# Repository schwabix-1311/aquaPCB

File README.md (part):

# aquaPCB

Raspberry Pi base board for [aquaPi](https://github.com/schwabix-1311/aquaPI), the
modular aquarium controller. v2 is a head unit that also fits Robo-Tank v3 modules, cables
and power bars (through adapter cables): one board with a 12-24 V supply input, six 5 A
power outputs, DC and LED ports with 7 PWM channels each, two power bar ports, six sensor
inputs, 1-Wire, four 0-5 V analog sockets on an ADS1115, and headers for a small display
and I²C add-ons. A cheaper **light** assembly of the same PCB is for aquaPi only - it is
**not** a Robo-Tank replacement (see [Light variant](#light-variant-aquapi-only)).

Most channels are plain GPIO, hardware PWM, 1-Wire or I²C ports that aquaPi discovers by
itself and offers in its Wiring editor. The channels on the two PCA9685 PWM expanders
(DC/LED ports, Q2/Q3/Q5/Q6, power bars) use aquaPi's PCA9685 driver, which finds the chips by
an I²C scan (0x40-0x47) and offers only the ports of the chips it finds. It ships with aquaPi 1.0
(branch `release/1.0`) and still has to be tested on real hardware.

> Status: **v2 layout complete** on `main` (2026-10-23): schematic ERC clean, board fully
> routed, DRC without errors (silkscreen warnings only; the deliberate overlap of the ADC
> socket courtyards is waived by a rule in `kicad/aquaPCB.kicad_dru`). No prototypes built
> yet; the [first prototype order](#first-prototype-order-5-light-boards-2-upgrade-kits) (5 light
> boards, 2 upgrade kits) is planned, the [open questions](#open-questions-asked-to-robo-tank-or-measure)
> to Robo-Tank are still open. v1 (tag `v1.0.1`, branch `release/v1`, layout complete,
> DRC clean) stays the restart point. Sections marked *v1* below still describe v1; v2
> changes are in the [v2 plan](#v2-plan-robo-tank-v3-compatible-head-unit).
> Not a beginner kit: SMD parts are assembled by the PCB fab (JLCPCB economic PCBA);
> only through-hole connectors are hand-soldered.

## Key figures

```
Supply          12-24 V DC, 8 A max total, 10 A fuse (parts rated >= 40 V; 24 V not yet validated)
Pi              Zero 2 W plugged on face-up, powered from the board; Pi 3 via 40-pin ribbon;
                Pi 4/5 with their own power supply (JP1 open)
Power outputs   6x low-side MOSFET, 5 A each, 6.5 A total (up to ~7 A, see current budget);
                Q1/Q4 on hardware PWM, Q2/Q3/Q5/Q6 on PCA9685 #1 (shared with LED port pins 2..5)
PWM ports       DC port + LED port, 7 channels each, 0-5 V PWM (PCA9685 #1, 74HCT244),
                2x4 box headers with the Robo-Tank v3 pinout
Power bars      2 ports x 8 outlets, 3.3 V logic (PCA9685 #2), 2x5 box headers for an IDC DB9
                adapter; 2 hardware backup float inputs for bar 1 outlets 1/2
Inputs          6x sensor inputs, 5 V tolerant (GPIO 5,6,20-23), 2x4 box header
1-Wire          GPIO4, 1x3 pin header (bus: several sensors on one header)
Analog          ADS1115, 16 bit, 4x 0-5 V sockets; pH/ORP amplifiers on add-on modules
Expansion       2x 3.3 V I2C header, SPI display header
Board           100 x 100 mm, 2 layers, 1 oz Cu
```

No mains voltage on this board. Mains loads (heater, pumps) are switched by external
SSRs or relay modules on the Q outputs, or by Robo-Tank power bars.

## Block diagram

*v1 - for v2 see [aquaPCB v2 connectors](#aquapcb-v2-connectors) and [v1 -> v2 changes](#v1---v2-changes).*

```
 12 V in ──[fuse 8A]───[rev.pol. P-FET]──┬──[TVS]── V_IN rail ─────────────┐
                                         │                                  │
                                    [buck 5V/3A]──┬── jumper "5V→Pi" ──> Pi 5V
                                                  │                         │
                                             [LDO 3V3]── ADC, sensors, display
                                                                            │
   Pi GPIO ──> [74HCT244, 5V] ──> gate ──> Q1..Q6 MOSFET ──> terminals (+V_IN / OUT)
   Pi GPIO ──> [ULN2803A] ─────────────> S1..S4 ──> terminals (+5V|+V_IN / OUT)
   IN1..IN4 terminals ──[1k + clamp, 10k pull-up]──> Pi GPIO
   1-Wire terminals ──[4k7 pull-up, ESD]──> GPIO4
   I2C (GPIO2/3) ──> 2x I2C header
                └──> ADS1115 ──< pH buffer ──< BNC ;  module input (0..5 V) ;  AIN3 terminal
   SPI0 + DC/RST ──> display header
```

## Pin map (BCM numbering)

*v1 - for v2 see [aquaPCB v2 connectors](#aquapcb-v2-connectors) and [v1 -> v2 changes](#v1---v2-changes).*

Outputs sit on GPIO 9 and above only: those pins default to pull-down at boot, so no load
switches on while the Pi boots. GPIO 0..8 default to pull-up and are used for inputs and
buses only.

```
GPIO  function            GPIO  function
 0    reserved (ID EEPROM) 14    unused (not connected)
 1    reserved (ID EEPROM) 15    unused (not connected)
 2    I2C SDA              16    Q5  power out
 3    I2C SCL              17    S1  SSR out
 4    1-Wire               18    Q1  power out, PWM0 (light)
 5    IN1                  19    Q4  power out, PWM1 (fan)
 6    IN2                  20    IN3
 7    SPI CE1              21    IN4
 8    SPI CE0              22    S2  SSR out
 9    SPI MISO             23    S3  SSR out
10    SPI MOSI             24    display RST
11    SPI SCLK             25    display DC
12    Q2  power out        26    Q6  power out
13    Q3  power out        27    S4  SSR out
```

All GPIOs except 14/15 are in use (14/15 stay free: no UART console, customers rarely
have a USB-serial adapter). Further expansion goes over I²C (e.g. PCA9685 PWM breakout,
MCP23017 IO expander).

Raspberry Pi OS settings: `dtoverlay=pwm-2chan,pin=18,func=2,pin2=19,func2=2`,
`dtoverlay=w1-gpio,gpiopin=4`, `dtparam=i2c_arm=on`, `dtparam=spi=on` (display only).

## Circuit blocks

*v1 - for v2 see [aquaPCB v2 connectors](#aquapcb-v2-connectors) and [v1 -> v2 changes](#v1---v2-changes).*

### Power input
- 2-pin push-in terminal, 8 A fuse in a Littelfuse OMNI-BLOK holder (replaceable Nano2
  fuse; common 5x20 mm PCB holders are only rated 6.3 A). 8 A is the board's total current
  limit, set by the terminals' rating (8 A IEC per contact).
- Reverse-polarity protection: P-channel MOSFET in the positive line, gate via resistor
  to GND with a 15 V zener clamp (needed only above ~18 V, kept for 24 V readiness).
- TVS SMBJ33A across V_IN, bulk electrolytic 470 µF / 50 V.

### 5 V and 3.3 V
- Buck converter TPS54360B (60 V input, 3.5 A), non-synchronous with SS54 catch diode and
  10 µH / 5.4 A inductor, set to 5 V / 3 A. 3 A covers Pi Zero 2 W through Pi 4.
  Based on TI's 5 V design example (datasheet SNVSB93, fig. 32), values moved to JLC basic
  parts: RT 150 k (644 kHz), feedback 12 k / 2.2 k (5.16 V), compensation 12 k + 10 nF,
  47 pF, 2x 47 µF output. EN left open (internal 4.3 V UVLO).
- Jumper "5V→Pi" feeds the Pi through its GPIO header 5 V pins. Leave it **open** when the
  Pi has its own USB power supply (always for Pi 5).
- 3.3 V LDO (AMS1117-3.3) from 5 V for ADC, 1-Wire, inputs and display, so peripherals
  don't load the Pi's own regulator.

### Power outputs Q1..Q6
Identical low-side switches, terminal pair +V_IN / OUT per channel, 5 A each (8 A in total
for the whole board).
- 74HCT244 on 5 V as gate driver: accepts 3.3 V logic (V_IH 2.0 V), drives gates at 5 V,
  and keeps the Pi's GPIOs isolated from the power stage.
- 100 Ω gate resistor, 10 kΩ gate pull-down (output stays off when the Pi is absent or
  booting), logic-level N-MOSFET, 40 V, DPAK (e.g. AOD4184A, ~9 mΩ at V_GS 4.5 V).
- SS54 Schottky freewheel diode OUT → +V_IN for fans, pumps, solenoids.
- Status LED per channel.
- Q1/Q4 on hardware PWM (GPIO18/19) for dimming LED lamps and 2-wire fans. 4-wire PC-fan
  PWM input is not supported. The GPIO order Q1 18, Q2 12, Q3 13, Q4 19 follows the Pi
  header, so the GPIO → 74HCT244 → gate lines route without crossings.

Why not drive the MOSFET directly from the GPIO (e.g. IRLB8721)? It works with typical
parts, but R_DS(on) is only specified from V_GS 4.5 V while V_th may reach 2.35 V, so a
worst-case part runs half-on at 3.3 V and heats up; the gate floats during boot; a
gate-drain short puts the load supply onto the Pi; and 30 V V_DS leaves no margin for 24 V.
The buffer costs about €0.60 per board.

### SSR outputs S1..S4
- ULN2803A (SOIC-18), open-collector sink with built-in flyback diodes.
- Terminal pair per channel: supply (+5 V or +V_IN, selected by jumper) and OUT.
- Drives SSRs with 3..32 V DC control input or relay modules.
- The four unused ULN2803A channels stay unconnected (inputs open; the internal resistors keep
  them off).

### Digital inputs IN1..IN4
3-pin terminal 3V3 / IN / GND for float switches, level sensors, push buttons.
1 kΩ series resistor, 10 kΩ pull-up to 3.3 V, BAT54S clamp to 3.3 V and GND.

### 1-Wire
GPIO4 with 4.7 kΩ pull-up to 3.3 V; one 3-pin terminal (GND / DQ / 3V3), so both
3-wire and parasitic-powered (GND / DQ only) DS18B20 sensors work. ESD protection diode.

### ADS1115 and pH
- ADS1115 on 3.3 V directly on the Pi's I²C bus (matching logic levels, no level shifter),
  address 0x48 by default, 0x49 by solder jumper.
- All inputs are read **single-ended**, as aquaPi's ADS1115 driver does today.
- Requirements behind this design: good probe lifetime; ~0.1 pH stability is enough, since
  aquaPi's ScaleAux calibration removes offset and slope. Derived from the hand-built
  controller (PH-4502C amplifier with 10 MΩ / 4.7 nF styroflex input filter, probe life > 2
  years).
- AIN0: on-board pH amplifier, like the PH-4502C but with a low-leakage input. Right-angle BNC
  jack at the left board edge (see Mechanical),
  10 MΩ in series, styroflex capacitor to the probe reference, TLV9062 CMOS buffer on 3.3 V
  (0.5 pA input bias). The probe reference (BNC shell) sits at PH_REF = 1.65 V (3.3 V / 2,
  buffered by the second op-amp half), so AIN0 reads 1.65 V ± 59 mV/pH.
- Probe load: only the op-amp input (0.5 pA typical, ≈ 10¹² Ω or more) and the leakage of
  the polystyrene capacitor. No ceramic capacitor or clamp on the high-impedance input:
  MLCC leakage (only specified to ~10 GΩ) would dominate.
- 50 Hz suppression (filter pumps), two stages: 10 MΩ / 6.8 nF styroflex at the input
  (68 ms; together with the electrode's 100 MΩ..1 GΩ: 0.7..7 s), then 10 k / 10 µF after the
  buffer (1.6 Hz, about −30 dB at 50 Hz). Styroflex values 47 pF..6.8 nF are available.
- Ground-loop insurance: 1 MΩ between the PH_REF buffer and the BNC shell. Nothing in the
  tank is grounded today; if that ever changes (a grounded sensor), the DC current through
  the reference electrode stays below ~1.7 µA instead of mA. The reading goes visibly wrong,
  the probe survives. In normal operation only pA flow through it. (A fully isolated pH
  stage was designed and dropped: ~€3 per board for a case that doesn't occur.)
- Layout of the high-impedance node (PH_BNC / PH_IN: BNC centre, 10 MΩ, styroflex lead,
  op-amp pin 3), replacing the point-to-point "air wiring" of the hand-built version:
  - guard ring on both layers around all of it, on net PH_BUF (the buffer output follows
    the input within the op-amp offset, so input-to-guard leakage is ~1.6 mV / R_leak:
    femtoamps on a clean board); stray leakage from other nets ends in the guard;
  - non-plated milled slots between the BNC centre pad and the shell pads, and around the
    input pads, to cut surface leakage paths;
  - shortest possible node, solder mask on, no silkscreen inside the guard, flux washed off
    (and the board dried) after hand-soldering; optional conformal coating of the pH corner.
- AIN1: PH_REF, as a monitor and for a later AIN0−AIN1 differential reading if the driver
  gets support for it.
- AIN2: module input for 5 V amplifier boards (e.g. the PH-4502C from probe kits, ORP or
  conductivity boards), terminal +5 V / SIG / GND. Divider 10 k / 20 k, fitted by default,
  maps 0..5 V to 0..3.33 V (leave the 20 k off for 1:1 up to 3.3 V); with 10 µF a 2.4 Hz
  low-pass; clamped to 0..3.3 V.
- AIN3: terminal 3V3 / AIN3 / GND for other 0..3.3 V sensors, 1 k / 100 nF, clamped.

### Display and I²C expansion
- 2x 4-pin I²C header, pin order GND / VCC / SCL / SDA (common SSD1306 OLED modules).
- 8-pin SPI header for ST7735 / ILI9341 TFTs: CE0, CE1, MOSI, MISO, SCLK, DC, RST,
  backlight to 3.3 V via jumper.

## Schematic

*v1 - for v2 see [aquaPCB v2 connectors](#aquapcb-v2-connectors) and [v1 -> v2 changes](#v1---v2-changes).*

KiCad 10 project in [kicad/](kicad): root sheet `aquaPCB.kicad_sch` with six sub-sheets
(power, Pi connector, power outputs, SSR outputs, inputs/1-Wire/display, ADC/pH) and a
project footprint library `aquaPCB.pretty` (Littelfuse OMNI-BLOK fuse holder).

The first v1 draft was generated by `tools/gen_schematic_v1.py` from the pin map and BOM:
every pin ends in a short stub with a net label or power symbol, so the drawing is a
readable netlist rather than a hand-routed schematic. Once the schematic is edited in
eeschema, the `.kicad_sch` files are the source of truth; the generator is **retired**
and refuses to overwrite existing schematics (`--force` only for a fresh draft).

```
python3 tools/gen_schematic_v1.py                     # (re)generate the v1 draft
for f in kicad/*.kicad_sch; do kicad-cli sch upgrade "$f"; done
kicad-cli sch erc --severity-all kicad/aquaPCB.kicad_sch
```

C1 diameter checked 2026-11-17: the footprint is D10, so C1 must be a 10 mm can (Rubycon
50ZLJ470M10X20, see [BOM.md](BOM.md)); a 12.5 mm 470 µF / 50 V touches D2.
The BNC footprint (`aquaPCB.pretty`) is made from the LCSC/EasyEDA pad data and the maker drawing.

## Build options

Optional parts carry KiCad's **DNP** (Do Not Populate) flag: their footprints stay on the board,
but they are left out of the BOM and the pick-and-place file. They are all through-hole pin
headers, so they can be soldered in later if needed.

```
J23   second I2C header
J24   SPI display header
JP3   display backlight jumper
```

Export for JLCPCB without them: `kicad-cli sch export bom --exclude-dnp ...` and
`kicad-cli pcb export pos --exclude-dnp ...`. Further options (e.g. on-board pH amplifier vs.
external amplifier board on AIN2, Pi Zero socket vs. Pi 3/4 box header) can become KiCad 10
design variants once they are needed.

## Mechanical

- 100 x 100 mm, 4x M3 mounting holes.
- One 2x20 footprint with normal (not mirrored) pin numbering, fitted with either
  - a 2x20 female socket: Pi Zero 2 W sits **face-up** on it, with its 2x20 pin header
    soldered on the Zero's underside (pins pointing down; use a Zero 2 W without
    pre-soldered header, not the WH). The header side is held by the plug connection, the
    opposite side by two M2.5 x 11 mm standoffs in the Zero's outer mounting holes (H5/H6,
    58 mm apart). No holes next to the header, so the larger box header fits as well.
    Face-up keeps SoC cooling, SD card and LED accessible; or
  - a 40-pin box header: Pi 3/4 connect through a standard IDC ribbon cable.
  A face-down Zero would need a mirrored footprint and could not share it with the ribbon.
- pH BNC: right-angle jack HanElectricity BNC-Q9-50KWE at the left board edge. Its body front face is
  flush with the edge; nut and barrel (d 9.5 mm, thread 1/2-28UNEF) protrude 21.4 mm, enclosure cutout
  d 12.9 mm. The whole shell (pin and both legs) is the probe reference PH_SHELL, not GND: in a metal
  enclosure it must be insulated from the wall (plastic enclosure or insulating bushing). Its insulation
  resistance is only specified at ≥ 5 GΩ (POM insulator); with a 1 GΩ electrode that is a worst-case
  gain error of ~17 % (typical parts are far better and ScaleAux calibrates the slope), but humidity can
  change it - a PTFE-insulated BNC would be the upgrade if readings drift.
- All terminals are push-in spring terminals (Kangnex WJ250B, 3.5 mm pitch, staggered pins) on the
  board edges, wire entry facing outwards: wires up to 1.5 mm² / 16 AWG, strip 9–10 mm; solid wire
  or ferrules push in, the button releases.
  The footprints have a hole in both staggered pin rows for every pole, so the MAX MX250-B
  (LCSC C7470116 / C7470117) fits as a drop-in alternative; when routing, join both holes of
  each pole.
- All terminals on the board edges; power path along one edge; the analog/pH corner away
  from the switching outputs.

## Current budget and copper

All current enters at J1 (8 A continuous, set by the terminal; 10 A fuse F1). Besides the six power outputs only the 5 V buck (U1) draws from
V_IN (plus about 2-3 mA for the power LED and the reverse-polarity FET's gate resistor); the Pi, the
ports and all logic hang on the buck's 5 V output.

**Power outputs Q1..Q6: max 5 A each, 6.5 A in total** (printed on the board). What is left of the
8 A input for the outputs depends on the 5 V load (buck at 5.16 V, efficiency 82-89 %):

```
5 V load (buck output)                          V_IN current       left for Q1..Q6
                                                12 V     24 V      12 V     24 V
typical: Pi Zero 2 W, a few sensors   ~0.55 A   0.28 A   0.15 A    7.7 A    7.8 A
Pi Zero 2 W, feeder running, all DC/LED
  and power bar outputs on            ~2.1 A    1.0 A    0.53 A    7.0 A    7.5 A
buck design limit                      3 A      1.47 A   0.75 A    6.5 A    7.2 A
```

6.5 A holds for any 5 V load the buck can deliver at 12 V; with a Pi Zero 2 W about 7 A are
available. 5 V loads behind those rows (typical / max):

```
Pi Zero 2 W (JP1 fitted)                                         0.35 A / 1.0 A
+5V_EXT through PTC F2: sensors, analog sockets, 1-Wire, and the
  feeder via +3V3_EXT (U11); PTC hold 1.1 A, trip 2.2 A          0.1 A  / 1.1 A
74HCT244 x3: Q status LEDs, 14 DC/LED port channels (6 mA each)  0.035 A / 0.1 A
+3V3 via U2: 2x PCA9685, 16 power bar outputs, ADS1115,
  display, I2C add-ons                                           0.06 A / 0.3 A
```

**Pi 4 and Pi 5 need their own power supply** (official PSU; leave JP1 open so the two supplies
don't meet). A Pi 4 alone may draw 3 A (Pi 5: 5 A), which together with the ports exceeds the 3 A
buck, and the 40-pin ribbon carries 5 V on only two wires. A Pi Zero 2 W (plugged on) and a Pi 3
(ribbon, up to about 2 A) are powered from the board through JP1.

Copper (1 oz, IPC-2221 temperature rise for an outer layer at the design current). Target: at most
10 °C even with this pessimistic method, which treats every run as a long conductor; short runs next
to large pads stay cooler. Parallel F/B runs share the current roughly by width.

```
Path                          current  copper                                  rise
J1 -> F1 -> Q10 (VIN_RAW)       8 A    3 mm on F and B in parallel             ~5 °C
F1 -> Q10 drain                 8 A    5.5 mm F, 1.4 mm between the pads       ~9 °C
Q10 source -> terminals (VIN)   8 A    source pad -> 10 vias -> 3 mm B         ~8 °C
                                       + 2 mm F in parallel up to J4
Q1..Q6 output -> terminal       5 A    3 mm                                    ~9 °C
MOSFET source -> GND            5 A    9 vias each into the B.Cu GND plane
J1 GND -> GND plane (return)    8 A    thermal relief, 7 spokes of 1.0 mm      ~2 °C
                                       (J1 only; 0.5 mm elsewhere) + 2x 1.0 mm F
buck input                       1 A   1.0 mm                                  ~1 °C
buck switch node SW (short)    2.1 A   1.5 mm                                  ~4 °C
5 V: L1 -> JP1                 2.1 A   1.5 mm                                  ~4 °C
5 V: JP1 -> Pi (5V_PI)           2 A   1.5 mm (Pi Zero 2 W / Pi 3 only)        ~3 °C
+5V -> F2 / U2                 1.4 A   0.75 mm                                 ~5 °C
+5V_EXT / +3V3_EXT          1.1 / 0.5 A 0.5 mm                                 ~5 / ~1 °C
signals                       < 0.1 A  0.25 mm
```

The 5 V currents assume a Pi 4/5 on its own supply (see above); the buck itself is sized for 3 A.

Component temperatures (estimate, ±30 %; rise above ambient, 1 oz copper areas as routed), at full
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
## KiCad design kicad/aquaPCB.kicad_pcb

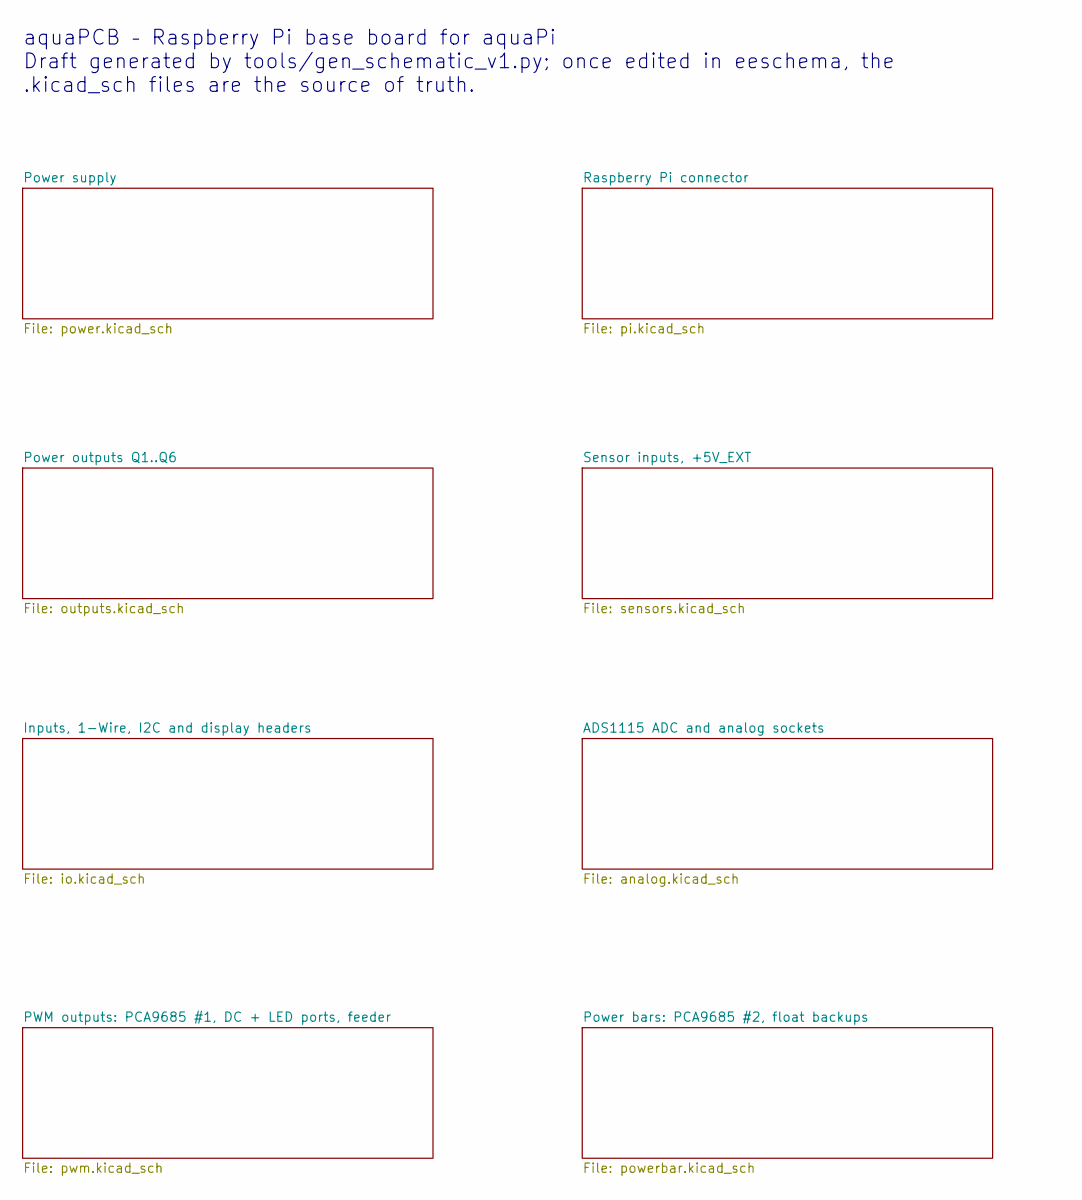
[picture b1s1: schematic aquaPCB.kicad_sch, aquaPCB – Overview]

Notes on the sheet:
aquaPCB – Raspberry Pi base board for aquaPi Draft generated by tools/gen_schematic_v1.py; once edited in eeschema, the .kicad_sch files are the source of truth.

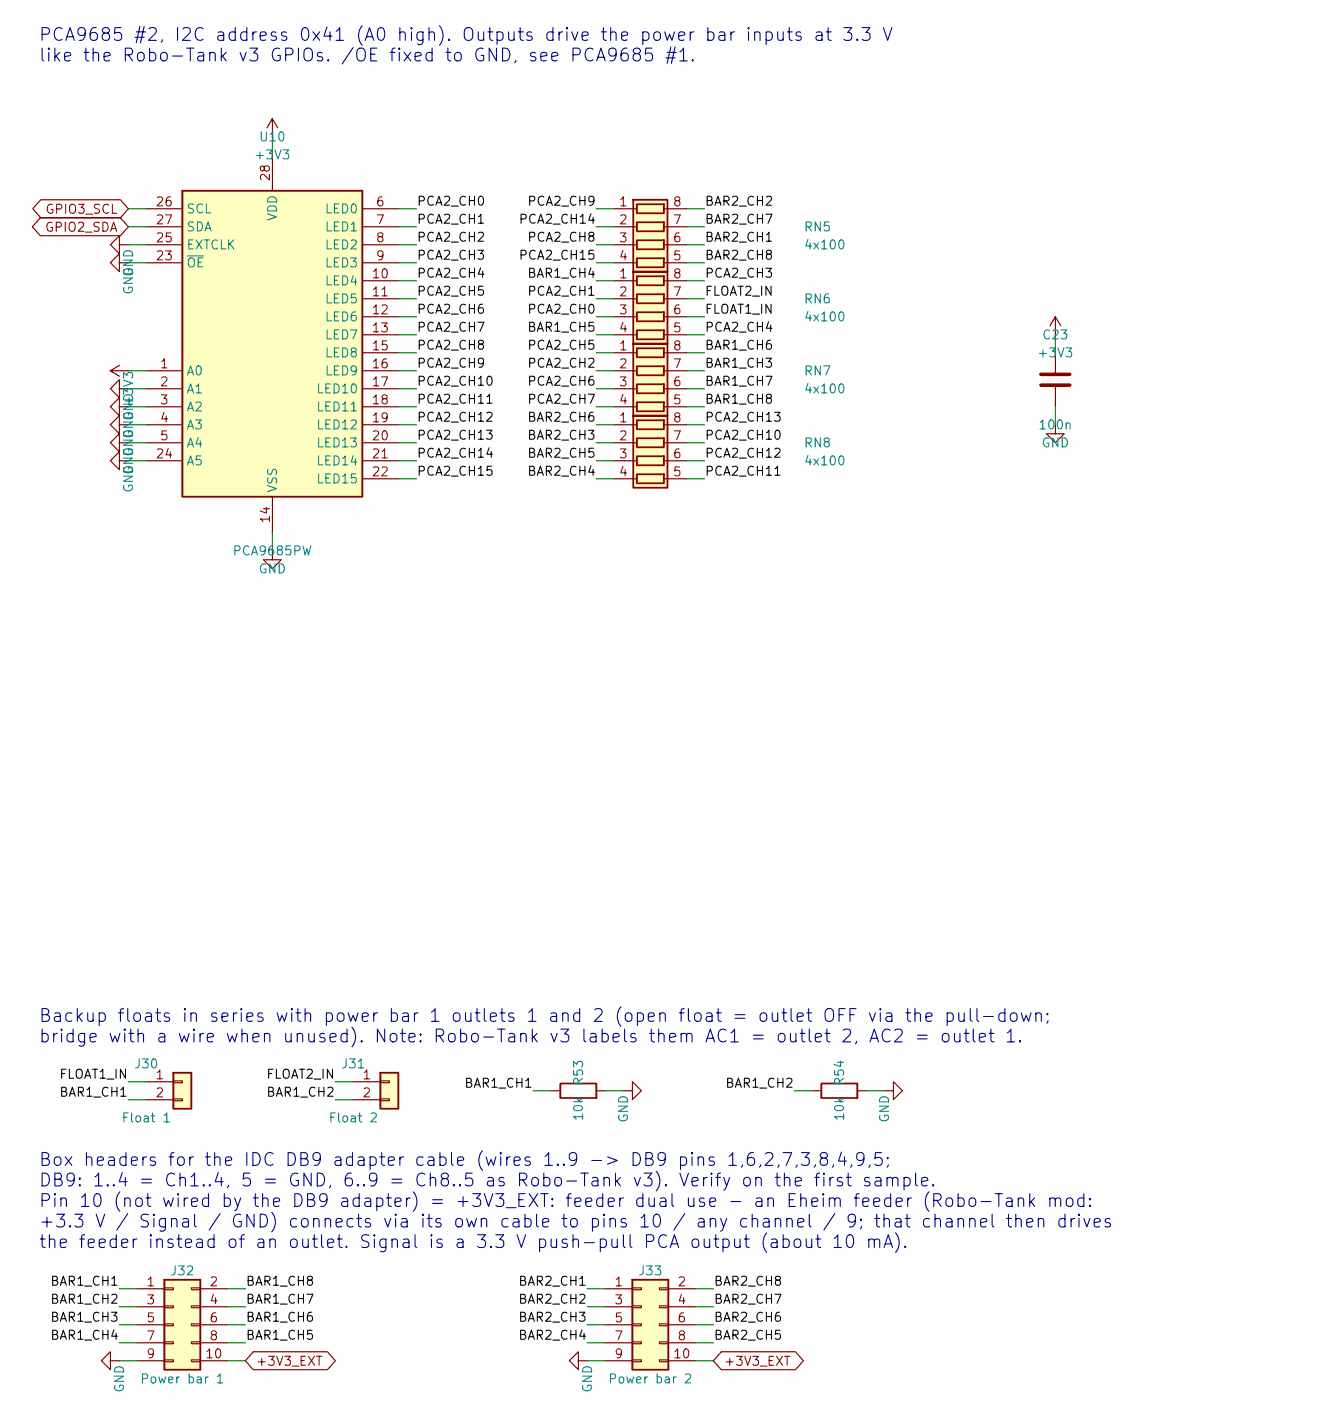
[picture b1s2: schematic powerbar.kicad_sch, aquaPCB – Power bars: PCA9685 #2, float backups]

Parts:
C23: 100n; C_0805_2012Metric; LCSC C49678
J30: Float 1; PinHeader_1x02_P2.54mm_Vertical
J31: Float 2; PinHeader_1x02_P2.54mm_Vertical
J32: Power bar 1; IDC-Header_2x05_P2.54mm_Vertical
J33: Power bar 2; IDC-Header_2x05_P2.54mm_Vertical
R53, R54: 10k; R_0603_1608Metric; LCSC C25804
RN5, RN6, RN7, RN8: 4x100; R_Array_Convex_4x0603; LCSC C25506
U10: PCA9685PW; TSSOP-28_4.4x9.7mm_P0.65mm; LCSC C2678753

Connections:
+3V3: C23.1, U10.1 (A0), U10.28 (VDD); also elsewhere on the board
+3V3_EXT: J32.10, J33.10; also elsewhere on the board
/Power bars: PCA9685 #2, float backups/BAR1_CH1: J30.2, J32.1, R53.1
/Power bars: PCA9685 #2, float backups/BAR1_CH2: J31.2, J32.3, R54.1
/Power bars: PCA9685 #2, float backups/BAR1_CH3: J32.5, RN7.7 (R2.2)
/Power bars: PCA9685 #2, float backups/BAR1_CH4: J32.7, RN6.1 (R1.1)
/Power bars: PCA9685 #2, float backups/BAR1_CH5: J32.8, RN6.4 (R4.1)
/Power bars: PCA9685 #2, float backups/BAR1_CH6: J32.6, RN7.8 (R1.2)
/Power bars: PCA9685 #2, float backups/BAR1_CH7: J32.4, RN7.6 (R3.2)
/Power bars: PCA9685 #2, float backups/BAR1_CH8: J32.2, RN7.5 (R4.2)
/Power bars: PCA9685 #2, float backups/BAR2_CH1: J33.1, RN5.6 (R3.2)
/Power bars: PCA9685 #2, float backups/BAR2_CH2: J33.3, RN5.8 (R1.2)
/Power bars: PCA9685 #2, float backups/BAR2_CH3: J33.5, RN8.2 (R2.1)
/Power bars: PCA9685 #2, float backups/BAR2_CH4: J33.7, RN8.4 (R4.1)
/Power bars: PCA9685 #2, float backups/BAR2_CH5: J33.8, RN8.3 (R3.1)
/Power bars: PCA9685 #2, float backups/BAR2_CH6: J33.6, RN8.1 (R1.1)
/Power bars: PCA9685 #2, float backups/BAR2_CH7: J33.4, RN5.7 (R2.2)
/Power bars: PCA9685 #2, float backups/BAR2_CH8: J33.2, RN5.5 (R4.2)
/Power bars: PCA9685 #2, float backups/FLOAT1_IN: J30.1, RN6.6 (R3.2)
/Power bars: PCA9685 #2, float backups/FLOAT2_IN: J31.1, RN6.7 (R2.2)
/Power bars: PCA9685 #2, float backups/PCA2_CH0: RN6.3 (R3.1), U10.6 (LED0)
/Power bars: PCA9685 #2, float backups/PCA2_CH1: RN6.2 (R2.1), U10.7 (LED1)
/Power bars: PCA9685 #2, float backups/PCA2_CH2: RN7.2 (R2.1), U10.8 (LED2)
/Power bars: PCA9685 #2, float backups/PCA2_CH3: RN6.8 (R1.2), U10.9 (LED3)
/Power bars: PCA9685 #2, float backups/PCA2_CH4: RN6.5 (R4.2), U10.10 (LED4)
/Power bars: PCA9685 #2, float backups/PCA2_CH5: RN7.1 (R1.1), U10.11 (LED5)
/Power bars: PCA9685 #2, float backups/PCA2_CH6: RN7.3 (R3.1), U10.12 (LED6)
/Power bars: PCA9685 #2, float backups/PCA2_CH7: RN7.4 (R4.1), U10.13 (LED7)
/Power bars: PCA9685 #2, float backups/PCA2_CH8: RN5.3 (R3.1), U10.15 (LED8)
/Power bars: PCA9685 #2, float backups/PCA2_CH9: RN5.1 (R1.1), U10.16 (LED9)
/Power bars: PCA9685 #2, float backups/PCA2_CH10: RN8.7 (R2.2), U10.17 (LED10)
/Power bars: PCA9685 #2, float backups/PCA2_CH11: RN8.5 (R4.2), U10.18 (LED11)
/Power bars: PCA9685 #2, float backups/PCA2_CH12: RN8.6 (R3.2), U10.19 (LED12)
/Power bars: PCA9685 #2, float backups/PCA2_CH13: RN8.8 (R1.2), U10.20 (LED13)
/Power bars: PCA9685 #2, float backups/PCA2_CH14: RN5.2 (R2.1), U10.21 (LED14)
/Power bars: PCA9685 #2, float backups/PCA2_CH15: RN5.4 (R4.1), U10.22 (LED15)
GND: C23.2, J32.9, J33.9, R53.2, R54.2, U10.2 (A1), U10.3 (A2), U10.4 (A3), U10.5 (A4), U10.14 (VSS), U10.23 (~OE), U10.24 (A5), U10.25 (EXTCLK); also elsewhere on the board
GPIO2_SDA: U10.27 (SDA); also elsewhere on the board
GPIO3_SCL: U10.26 (SCL); also elsewhere on the board

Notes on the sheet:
PCA9685 #2, I2C address 0x41 (A0 high). Outputs drive the power bar inputs at 3.3 V like the Robo-Tank v3 GPIOs. /OE fixed to GND, see PCA9685 #1.
Backup floats in series with power bar 1 outlets 1 and 2 (open float = outlet OFF via the pull-down; bridge with a wire when unused). Note: Robo-Tank v3 labels them AC1 = outlet 2, AC2 = outlet 1.
Box headers for the IDC DB9 adapter cable (wires 1..9 -> DB9 pins 1,6,2,7,3,8,4,9,5; DB9: 1..4 = Ch1..4, 5 = GND, 6..9 = Ch8..5 as Robo-Tank v3). Verify on the first sample. Pin 10 (not wired by the DB9 adapter) = +3V3_EXT: feeder dual use - an Eheim feeder (Robo-Tank mod: +3.3 V / Signal / GND) co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

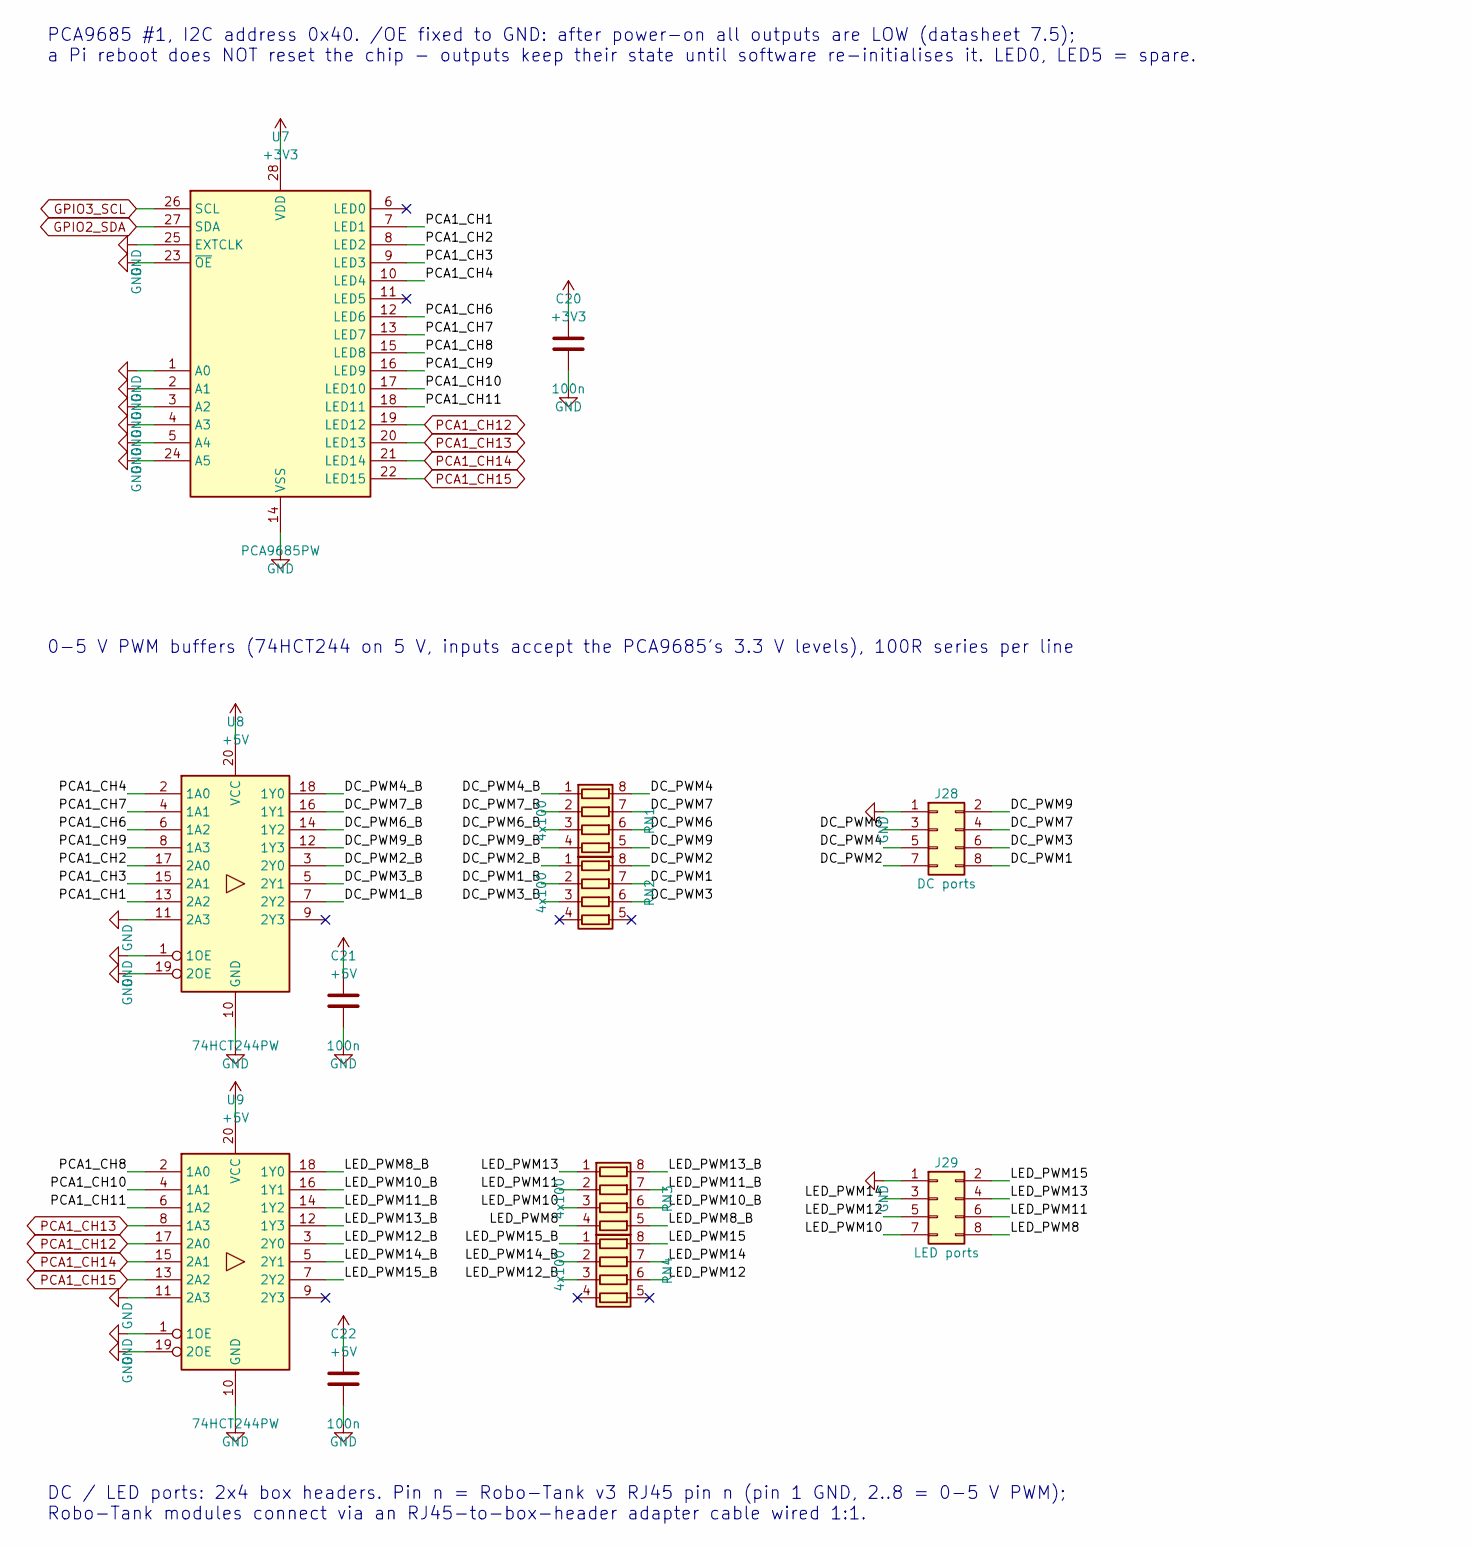
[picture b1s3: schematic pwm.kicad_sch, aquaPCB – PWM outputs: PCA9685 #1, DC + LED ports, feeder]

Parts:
C20, C21, C22: 100n; C_0805_2012Metric; LCSC C49678
J28: DC ports; IDC-Header_2x04_P2.54mm_Vertical
J29: LED ports; IDC-Header_2x04_P2.54mm_Vertical
RN1, RN2, RN3, RN4: 4x100; R_Array_Convex_4x0603; LCSC C25506
U7: PCA9685PW; TSSOP-28_4.4x9.7mm_P0.65mm; LCSC C2678753
U8, U9: 74HCT244PW; TSSOP-20_4.4x6.5mm_P0.65mm; LCSC C131088

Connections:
+3V3: C20.1, U7.28 (VDD); also elsewhere on the board
+5V: C21.1, C22.1, U8.20 (VCC), U9.20 (VCC); also elsewhere on the board
/PWM outputs: PCA9685 #1, DC + LED ports, feeder/DC_PWM1: J28.8, RN2.7 (R2.2)
/PWM outputs: PCA9685 #1, DC + LED ports, feeder/DC_PWM1_B: RN2.2 (R2.1), U8.7 (2Y2)
/PWM outputs: PCA9685 #1, DC + LED ports, feeder/DC_PWM2: J28.7, RN2.8 (R1.2)
/PWM outputs: PCA9685 #1, DC + LED ports, feeder/DC_PWM2_B: RN2.1 (R1.1), U8.3 (2Y0)
/PWM outputs: PCA9685 #1, DC + LED ports, feeder/DC_PWM3: J28.6, RN2.6 (R3.2)
/PWM outputs: PCA9685 #1, DC + LED ports, feeder/DC_PWM3_B: RN2.3 (R3.1), U8.5 (2Y1)
/PWM outputs: PCA9685 #1, DC + LED ports, feeder/DC_PWM4: J28.5, RN1.8 (R1.2)
/PWM outputs: PCA9685 #1, DC + LED ports, feeder/DC_PWM4_B: RN1.1 (R1.1), U8.18 (1Y0)
/PWM outputs: PCA9685 #1, DC + LED ports, feeder/DC_PWM6: J28.3, RN1.6 (R3.2)
/PWM outputs: PCA9685 #1, DC + LED ports, feeder/DC_PWM6_B: RN1.3 (R3.1), U8.14 (1Y2)
/PWM outputs: PCA9685 #1, DC + LED ports, feeder/DC_PWM7: J28.4, RN1.7 (R2.2)
/PWM outputs: PCA9685 #1, DC + LED ports, feeder/DC_PWM7_B: RN1.2 (R2.1), U8.16 (1Y1)
/PWM outputs: PCA9685 #1, DC + LED ports, feeder/DC_PWM9: J28.2, RN1.5 (R4.2)
/PWM outputs: PCA9685 #1, DC + LED ports, feeder/DC_PWM9_B: RN1.4 (R4.1), U8.12 (1Y3)
/PWM outputs: PCA9685 #1, DC + LED ports, feeder/LED_PWM8: J29.8, RN3.4 (R4.1)
/PWM outputs: PCA9685 #1, DC + LED ports, feeder/LED_PWM8_B: RN3.5 (R4.2), U9.18 (1Y0)
/PWM outputs: PCA9685 #1, DC + LED ports, feeder/LED_PWM10: J29.7, RN3.3 (R3.1)
/PWM outputs: PCA9685 #1, DC + LED ports, feeder/LED_PWM10_B: RN3.6 (R3.2), U9.16 (1Y1)
/PWM outputs: PCA9685 #1, DC + LED ports, feeder/LED_PWM11: J29.6, RN3.2 (R2.1)
/PWM outputs: PCA9685 #1, DC + LED ports, feeder/LED_PWM11_B: RN3.7 (R2.2), U9.14 (1Y2)
/PWM outputs: PCA9685 #1, DC + LED ports, feeder/LED_PWM12: J29.5, RN4.6 (R3.2)
/PWM outputs: PCA9685 #1, DC + LED ports, feeder/LED_PWM12_B: RN4.3 (R3.1), U9.3 (2Y0)
/PWM outputs: PCA9685 #1, DC + LED ports, feeder/LED_PWM13: J29.4, RN3.1 (R1.1)
/PWM outputs: PCA9685 #1, DC + LED ports, feeder/LED_PWM13_B: RN3.8 (R1.2), U9.12 (1Y3)
/PWM outputs: PCA9685 #1, DC + LED ports, feeder/LED_PWM14: J29.3, RN4.7 (R2.2)
/PWM outputs: PCA9685 #1, DC + LED ports, feeder/LED_PWM14_B: RN4.2 (R2.1), U9.5 (2Y1)
/PWM outputs: PCA9685 #1, DC + LED ports, feeder/LED_PWM15: J29.2, RN4.8 (R1.2)
/PWM outputs: PCA9685 #1, DC + LED ports, feeder/LED_PWM15_B: RN4.1 (R1.1), U9.7 (2Y2)
/PWM outputs: PCA9685 #1, DC + LED ports, feeder/PCA1_CH1: U7.7 (LED1), U8.13 (2A2)
/PWM outputs: PCA9685 #1, DC + LED ports, feeder/PCA1_CH2: U7.8 (LED2), U8.17 (2A0)
/PWM outputs: PCA9685 #1, DC + LED ports, feeder/PCA1_CH3: U7.9 (LED3), U8.15 (2A1)
/PWM outputs: PCA9685 #1, DC + LED ports, feeder/PCA1_CH4: U7.10 (LED4), U8.2 (1A0)
/PWM outputs: PCA9685 #1, DC + LED ports, feeder/PCA1_CH6: U7.12 (LED6), U8.6 (1A2)
/PWM outputs: PCA9685 #1, DC + LED ports, feeder/PCA1_CH7: U7.13 (LED7), U8.4 (1A1)
/PWM outputs: PCA9685 #1, DC + LED ports, feeder/PCA1_CH8: U7.15 (LED8), U9.2 (1A0)
/PWM outputs: PCA9685 #1, DC + LED ports, feeder/PCA1_CH9: U7.16 (LED9), U8.8 (1A3)
/PWM outputs: PCA9685 #1, DC + LED ports, feeder/PCA1_CH10: U7.17 (LED10), U9.4 (1A1)
/PWM outputs: PCA9685 #1, DC + LED ports, feeder/PCA1_CH11: U7.18 (LED11), U9.6 (1A2)
GND: C20.2, C21.2, C22.2, J28.1, J29.1, U7.1 (A0), U7.2 (A1), U7.3 (A2), U7.4 (A3), U7.5 (A4), U7.14 (VSS), U7.23 (~OE), U7.24 (A5), U7.25 (EXTCLK), U8.1 (1OE), U8.10 (GND), U8.11 (2A3), U8.19 (2OE), U9.1 (1OE), U9.10 (GND), U9.11 (2A3), U9.19 (2OE); also elsewhere on the board
GPIO2_SDA: U7.27 (SDA); also elsewhere on the board
GPIO3_SCL: U7.26 (SCL); also elsewhere on the board
PCA1_CH12: U7.19 (LED12), U9.17 (2A0); also elsewhere on the board
PCA1_CH13: U7.20 (LED13), U9.8 (1A3); also elsewhere on the board
PCA1_CH14: U7.21 (LED14), U9.15 (2A1); also elsewhere on the board
PCA1_CH15: U7.22 (LED15), U9.13 (2A2); also elsewhere on the board

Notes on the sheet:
0-5 V PWM buffers (74HCT244 on 5 V, inputs accept the PCA9685's 3.3 V levels), 100R series per line
DC / LED ports: 2x4 box headers. Pin n = Robo-Tank v3 RJ45 pin n (pin 1 GND, 2..8 = 0-5 V PWM); Robo-Tank modules connect via an RJ45-to-box-header adapter cable wired 1:1.
PCA9685 #1, I2C address 0x40. /OE fixed to GND: after power-on all outputs are LOW (datasheet 7.5); a Pi reboot does NOT reset the chip - outputs keep their state until software re-initialises it. LED0, LED5 = spare.

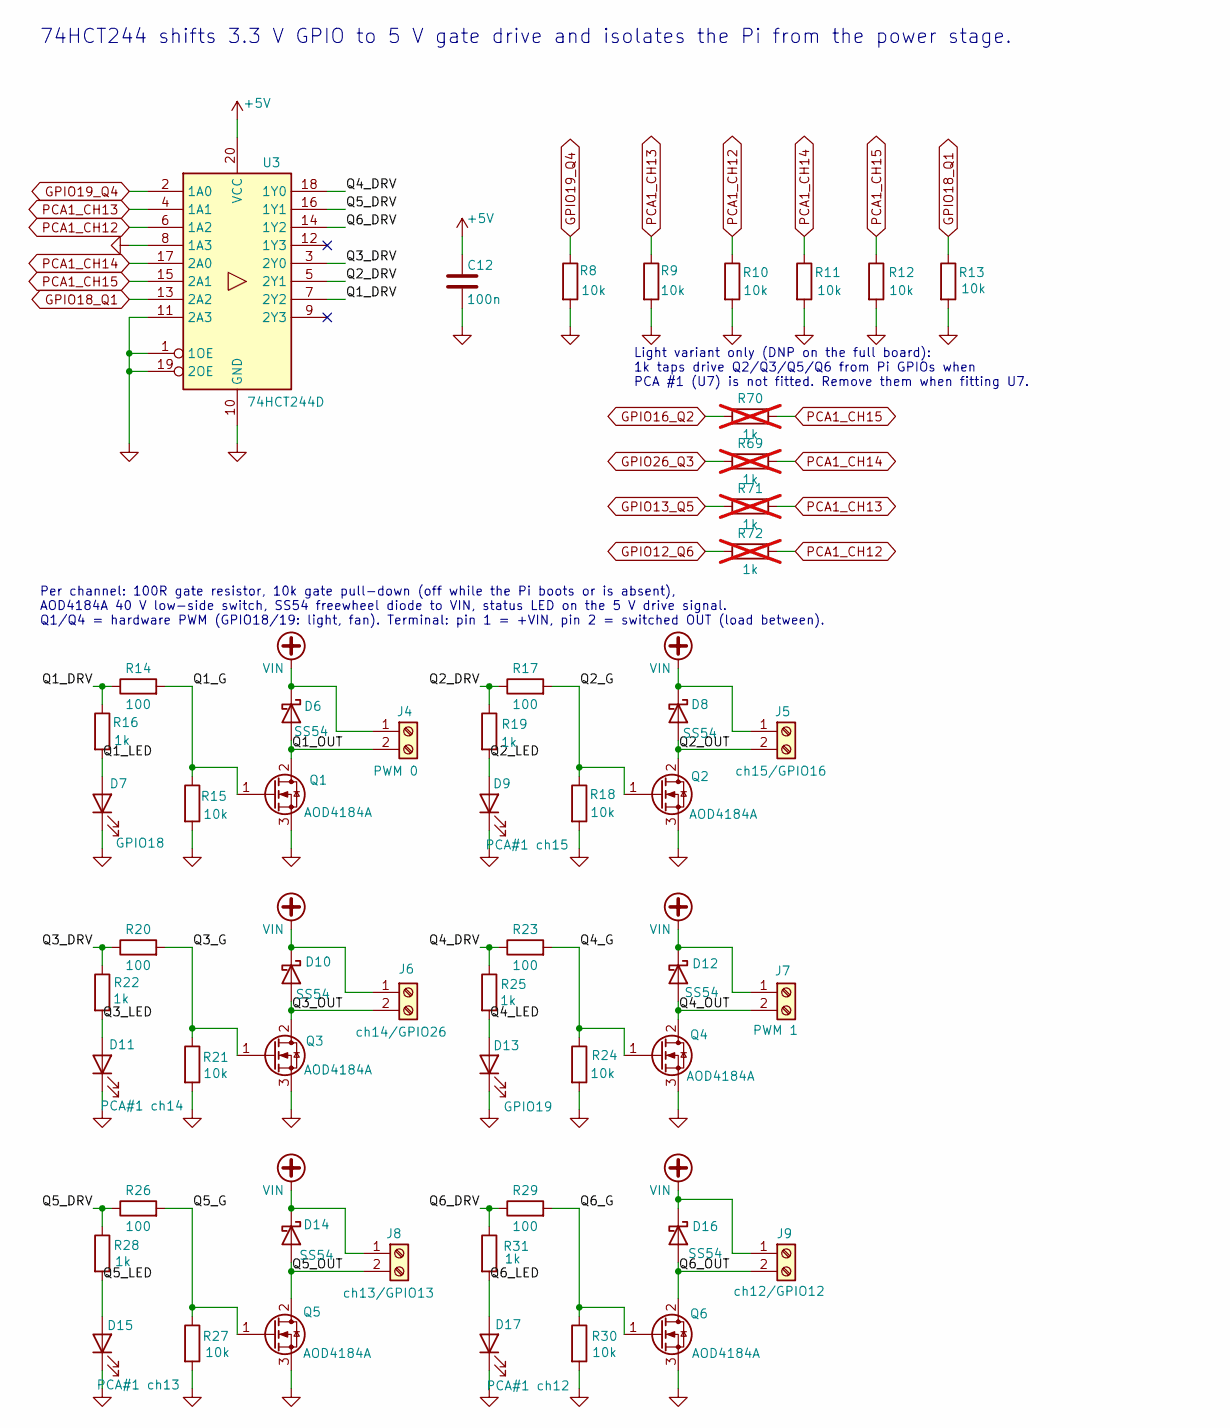
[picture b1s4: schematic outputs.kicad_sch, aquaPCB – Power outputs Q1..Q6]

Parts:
C12: 100n; C_0805_2012Metric; LCSC C49678
D6, D8, D10, D12, D14, D16: SS54; D_SMA; LCSC C22452
D7: GPIO18; LED_0805_2012Metric; LCSC C2297
D9: PCA#1 ch15; LED_0805_2012Metric; LCSC C2297
D11: PCA#1 ch14; LED_0805_2012Metric; LCSC C2297
D13: GPIO19; LED_0805_2012Metric; LCSC C2297
D15: PCA#1 ch13; LED_0805_2012Metric; LCSC C2297
D17: PCA#1 ch12; LED_0805_2012Metric; LCSC C2297
J4: PWM 0; TerminalBlock_Kangnex_WJ250B-3.5-02P_P3.50mm_Staggered; LCSC C8454
J5: ch15/GPIO16; TerminalBlock_Kangnex_WJ250B-3.5-02P_P3.50mm_Staggered; LCSC C8454
J6: ch14/GPIO26; TerminalBlock_Kangnex_WJ250B-3.5-02P_P3.50mm_Staggered; LCSC C8454
J7: PWM 1; TerminalBlock_Kangnex_WJ250B-3.5-02P_P3.50mm_Staggered; LCSC C8454
J8: ch13/GPIO13; TerminalBlock_Kangnex_WJ250B-3.5-02P_P3.50mm_Staggered; LCSC C8454
J9: ch12/GPIO12; TerminalBlock_Kangnex_WJ250B-3.5-02P_P3.50mm_Staggered; LCSC C8454
Q1, Q2, Q3, Q4, Q5, Q6: AOD4184A; TO-252-2; LCSC C99124
R8, R9, R10, R11, R12, R13, R15, R18, R21, R24, R27, R30: 10k; R_0805_2012Metric; LCSC C17414
R14, R17, R20, R23, R26, R29: 100; R_0805_2012Metric; LCSC C17408
R16, R19, R22, R25, R28, R31: 1k; R_0805_2012Metric; LCSC C17513
R69, R70, R71, R72: 1k; R_0603_1608Metric; LCSC C21190; not fitted
U3: 74HCT244D; SOIC-20W_7.5x12.8mm_P1.27mm; LCSC C5978

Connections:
+5V: C12.1, U3.20 (VCC); also elsewhere on the board
/Power outputs Q1..Q6/Q1_DRV: R14.1, R16.1, U3.7 (2Y2)
/Power outputs Q1..Q6/Q1_G: Q1.1 (G), R14.2, R15.1
/Power outputs Q1..Q6/Q1_LED: D7.2 (A), R16.2
/Power outputs Q1..Q6/Q1_OUT: D6.2 (A), J4.2, Q1.2 (D)
/Power outputs Q1..Q6/Q2_DRV: R17.1, R19.1, U3.5 (2Y1)
/Power outputs Q1..Q6/Q2_G: Q2.1 (G), R17.2, R18.1
/Power outputs Q1..Q6/Q2_LED: D9.2 (A), R19.2
/Power outputs Q1..Q6/Q2_OUT: D8.2 (A), J5.2, Q2.2 (D)
/Power outputs Q1..Q6/Q3_DRV: R20.1, R22.1, U3.3 (2Y0)
/Power outputs Q1..Q6/Q3_G: Q3.1 (G), R20.2, R21.1
/Power outputs Q1..Q6/Q3_LED: D11.2 (A), R22.2
/Power outputs Q1..Q6/Q3_OUT: D10.2 (A), J6.2, Q3.2 (D)
/Power outputs Q1..Q6/Q4_DRV: R23.1, R25.1, U3.18 (1Y0)
/Power outputs Q1..Q6/Q4_G: Q4.1 (G), R23.2, R24.1
/Power outputs Q1..Q6/Q4_LED: D13.2 (A), R25.2
/Power outputs Q1..Q6/Q4_OUT: D12.2 (A), J7.2, Q4.2 (D)
/Power outputs Q1..Q6/Q5_DRV: R26.1, R28.1, U3.16 (1Y1)
/Power outputs Q1..Q6/Q5_G: Q5.1 (G), R26.2, R27.1
/Power outputs Q1..Q6/Q5_LED: D15.2 (A), R28.2
/Power outputs Q1..Q6/Q5_OUT: D14.2 (A), J8.2, Q5.2 (D)
/Power outputs Q1..Q6/Q6_DRV: R29.1, R31.1, U3.14 (1Y2)
/Power outputs Q1..Q6/Q6_G: Q6.1 (G), R29.2, R30.1
/Power outputs Q1..Q6/Q6_LED: D17.2 (A), R31.2
/Power outputs Q1..Q6/Q6_OUT: D16.2 (A), J9.2, Q6.2 (D)
GND: C12.2, D7.1 (K), D9.1 (K), D11.1 (K), D13.1 (K), D15.1 (K), D17.1 (K), Q1.3 (S), Q2.3 (S), Q3.3 (S), Q4.3 (S), Q5.3 (S), Q6.3 (S), R8.2, R9.2, R10.2, R11.2, R12.2, R13.2, R15.2, R18.2, R21.2, R24.2, R27.2, R30.2, U3.1 (1OE), U3.8 (1A3), U3.10 (GND), U3.11 (2A3), U3.19 (2OE); also elsewhere on the board
GPIO12_Q6: R72.1; also elsewhere on the board
GPIO13_Q5: R71.1; also elsewhere on the board
GPIO16_Q2: R70.1; also elsewhere on the board
GPIO18_Q1: R13.1, U3.13 (2A2); also elsewhere on the board
GPIO19_Q4: R8.1, U3.2 (1A0); also elsewhere on the board
GPIO26_Q3: R69.1; also elsewhere on the board
PCA1_CH12: R10.1, R72.2, U3.6 (1A2); also elsewhere on the board
PCA1_CH13: R9.1, R71.2, U3.4 (1A1); also elsewhere on the board
PCA1_CH14: R11.1, R69.2, U3.17 (2A0); also elsewhere on the board
PCA1_CH15: R12.1, R70.2, U3.15 (2A1); also elsewhere on the board
VIN: D6.1 (K), D8.1 (K), D10.1 (K), D12.1 (K), D14.1 (K), D16.1 (K), J4.1, J5.1, J6.1, J7.1, J8.1, J9.1; also elsewhere on the board

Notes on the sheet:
Per channel: 100R gate resistor, 10k gate pull-down (off while the Pi boots or is absent), AOD4184A 40 V low-side switch, SS54 freewheel diode to VIN, status LED on the 5 V drive signal. Q1/Q4 = hardware PWM (GPIO18/19: light, fan). Terminal: pin 1 = +VIN, pin 2 = switched OUT (load between).
74HCT244 shifts 3.3 V GPIO to 5 V gate drive and isolates the Pi from the power stage.
Light variant only (DNP on the full board): 1k taps drive Q2/Q3/Q5/Q6 from Pi GPIOs when PCA #1 (U7) is not fitted. Remove them when fitting U7.

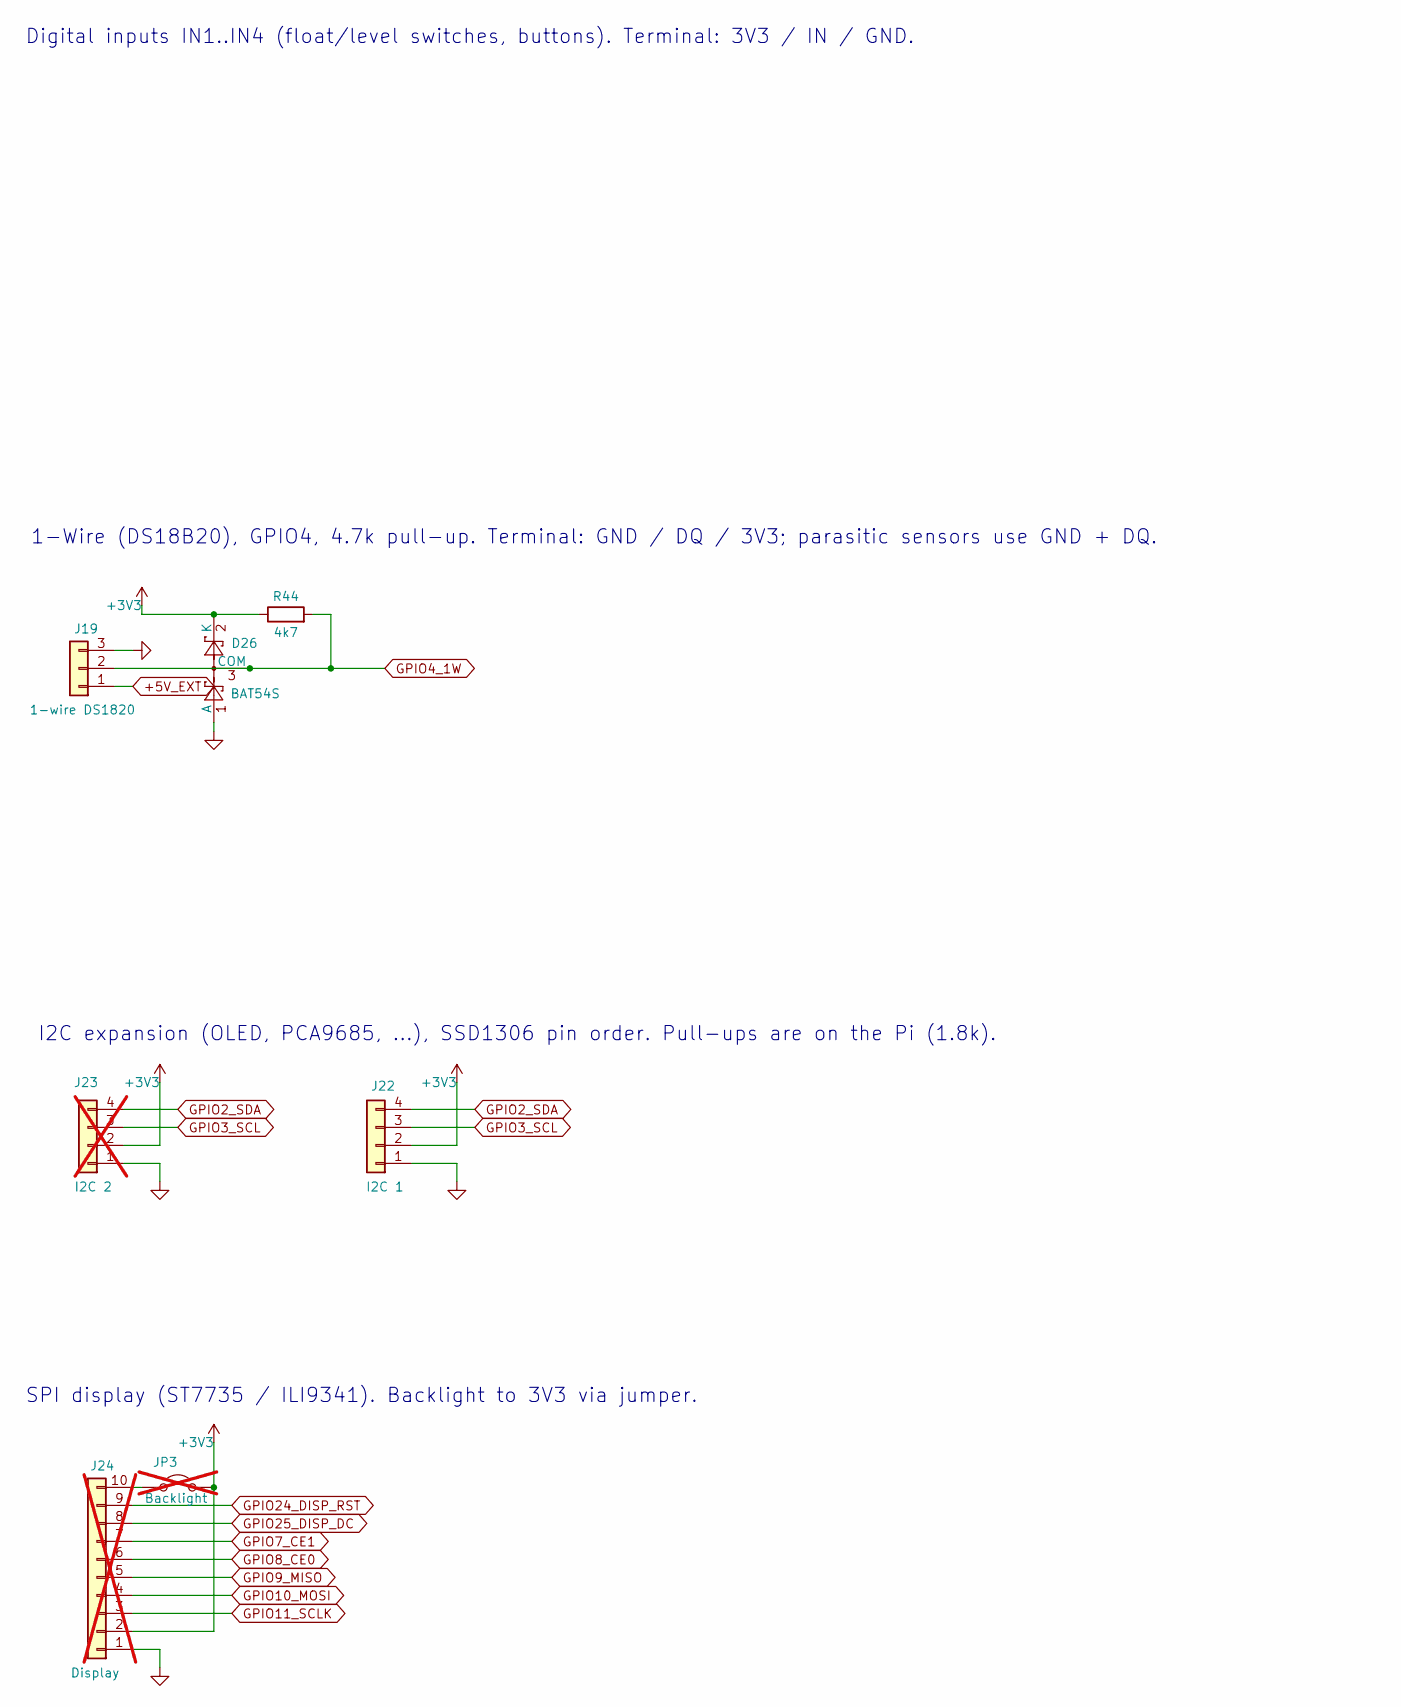
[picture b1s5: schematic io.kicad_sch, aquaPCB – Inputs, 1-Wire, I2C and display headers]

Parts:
D26: BAT54S; SOT-23; LCSC C7420333
J19: 1-wire DS1820; PinHeader_1x03_P2.54mm_Vertical
J22: I2C 1; PinHeader_1x04_P2.54mm_Vertical
J23: I2C 2; PinHeader_1x04_P2.54mm_Vertical; not fitted
J24: Display; PinHeader_1x10_P2.54mm_Vertical; not fitted
JP3: Backlight; PinHeader_1x02_P2.54mm_Vertical; not fitted
R44: 4k7; R_0805_2012Metric; LCSC C17673

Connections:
+3V3: D26.2 (K), J22.2, J23.2, J24.2, JP3.2 (B), R44.1; also elsewhere on the board
+5V_EXT: J19.1; also elsewhere on the board
GND: D26.1 (A), J19.3, J22.1, J23.1, J24.1; also elsewhere on the board
GPIO2_SDA: J22.4, J23.4; also elsewhere on the board
GPIO3_SCL: J22.3, J23.3; also elsewhere on the board
GPIO4_1W: D26.3 (COM), J19.2, R44.2; also elsewhere on the board
GPIO7_CE1: J24.7; also elsewhere on the board
GPIO8_CE0: J24.6; also elsewhere on the board
GPIO9_MISO: J24.5; also elsewhere on the board
GPIO10_MOSI: J24.4; also elsewhere on the board
GPIO11_SCLK: J24.3; also elsewhere on the board
GPIO24_DISP_RST: J24.9; also elsewhere on the board
GPIO25_DISP_DC: J24.8; also elsewhere on the board
unnamed: J24.10, JP3.1 (A)

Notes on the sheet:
I2C expansion (OLED, PCA9685, ...), SSD1306 pin order. Pull-ups are on the Pi (1.8k).
1-Wire (DS18B20), GPIO4, 4.7k pull-up. Terminal: GND / DQ / 3V3; parasitic sensors use GND + DQ.
Digital inputs IN1..IN4 (float/level switches, buttons). Terminal: 3V3 / IN / GND.
SPI display (ST7735 / ILI9341). Backlight to 3V3 via jumper.

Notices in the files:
README.md:
Licence:
Copyright Markus Kuhn 2026.
This source describes Open Hardware and is licensed under the CERN-OHL-S v2
(`SPDX-License-Identifier: CERN-OHL-S-2.0`), see [LICENSE](LICENSE).
You may redistribute and modify this source and make products using it under the terms
of the CERN-OHL-S v2 (https://ohwr.org/cern_ohl_s_v2.txt). This source is distributed
WITHOUT ANY EXPRESS OR IMPLIED WARRANTY, INCLUDING OF MERCHANTABILITY, SATISFACTORY
QUALITY AND FITNESS FOR A PARTICULAR PURPOSE. Please see the CERN-OHL-S v2 for applicable
conditions.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
kicad-v1/analog.kicad_sch:
CERN-OHL-S-2.0
